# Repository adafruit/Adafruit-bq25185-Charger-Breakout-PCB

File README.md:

## Adafruit bq25185 USB / DC / Solar Lithium Ion/Polymer Charger PCB

<a href="http://www.adafruit.com/products/6091"><br/>
Click here to purchase one from the Adafruit shop</a>

PCB files for the Adafruit bq25185 USB / DC / Solar Lithium Ion/Polymer Charger. 

Format is EagleCAD schematic and board layout
* https://www.adafruit.com/product/6091

### Description

We're always on the look out for better ways to make projects portable: being able to charge your battery in the most convenient manner will let projects run no matter what power is available. The Adafruit bq25185 USB / DC / Solar Charger Board uses the new bq25185 is a nifty charger chip which has a lot of flexibility for different kinds of batteries (LiPoly, LiIon or LiFePO4), charging rates (250mA, 500mA, or 1A) and power sources (USB, DC or solar). It's also a great value, so it's a good upgrade from MCP73833 or MCP73831-based charger boards.

To let folks really explore what this chip can do, we made a basic breakout board with all the things we find most useful: two ways to power/charge including a solar-friendly DC input, adjustable current and voltage, power path management, and status and control I/O.

* USB Type C connector with 5.1k CC resistors so it will work with any computer or power supply to get 5V and up to 1A
* Separate DC or Solar Input - Two pads on the side can be used to connect a 5 ~ 18V power supply, which can be used instead of USB. If the input is a solar panel, the charging chip will adjust the current draw so that the voltage does not dip below the battery, thus optimizing the solar power input. No large capacitor needed to stabilize it, and you get near-MPPT capability without the cost and complexity of MPPT.
* Default charge rate of 1A, but you can cut the IS jumper on the front and solder either jumper on the back to set the rate to 500mA or 250mA
* Default 3.7V nominal / 4.2V max battery chemistry/voltage for all modern 1-cell LiPoly or LiIon batteries. You can set this to 3.2V / 3.65V for LiFePO4 batteries by cutting the VS jumper on the front and soldering a jumper on the back
* Power Path to Load - If the load connector is drawing current while the USB / DC/Solar power is attached, it will default to drawing current from the charger and any left over current will go to the battery. That keeps your battery from constantly charging/discharging which will reduce the battery life. The max draw from USB / DC / Solar is still 1A, if you need more current it will come from the battery and the chip can provide up to 3A current spikes from the battery to the load output!
* Regulated 4.5V-max Load Output - no matter what voltage you have on the USB or DC / solar inputs, the Load output port will never go above 4.5V due to an internal voltage regulator. Keep this in mind, though, when dealing with high currents and high DC voltages as the LDO will make the board start to overheat and throttle the current.
* Three Status LEDs - Orange Charging LED, red Fault LED, and Green Power Good LED. The charge/fault pins are also available on the left side breakout pads.
* Thermistor - cut the TH trace and you can connect a 10K thermistor to the TH pad which will adjust the charge rate to keep the battery from overheating.
* Chip Enable to disable the charger.
* Mounting holes!

This board is pretty much plug-and-play. Change any jumpers you like and then connect your battery to the BATT port, and the LOAD goes to your circuit. Don't forget the LOAD will never go above 4.5V, but it can go as low as 3.0V if the battery is nearly empty. You can monitor the voltage on the battery and load via the secondary pads on the right side, if necessary.

To use with solar, pick up a 5~7V solar panel, and either cut the connector off to wire it directly, or use a 2.1mm adapter cable plus a 2.1mm terminal block to get two wires for the DC Input port.

If you need a board with higher charge current or a DC plug already on-board, check out the bq24074 which has up to 1.5A charge rate and a on-board 2.1mm DC jack.

### License

Adafruit invests time and resources providing this open source design, please support Adafruit and open-source hardware by purchasing products from [Adafruit](https://www.adafruit.com)!

Designed by Limor Fried/Ladyada for Adafruit Industries.

Creative Commons Attribution/Share-Alike, all text above must be included in any redistribution. 
See license.txt for additional details.

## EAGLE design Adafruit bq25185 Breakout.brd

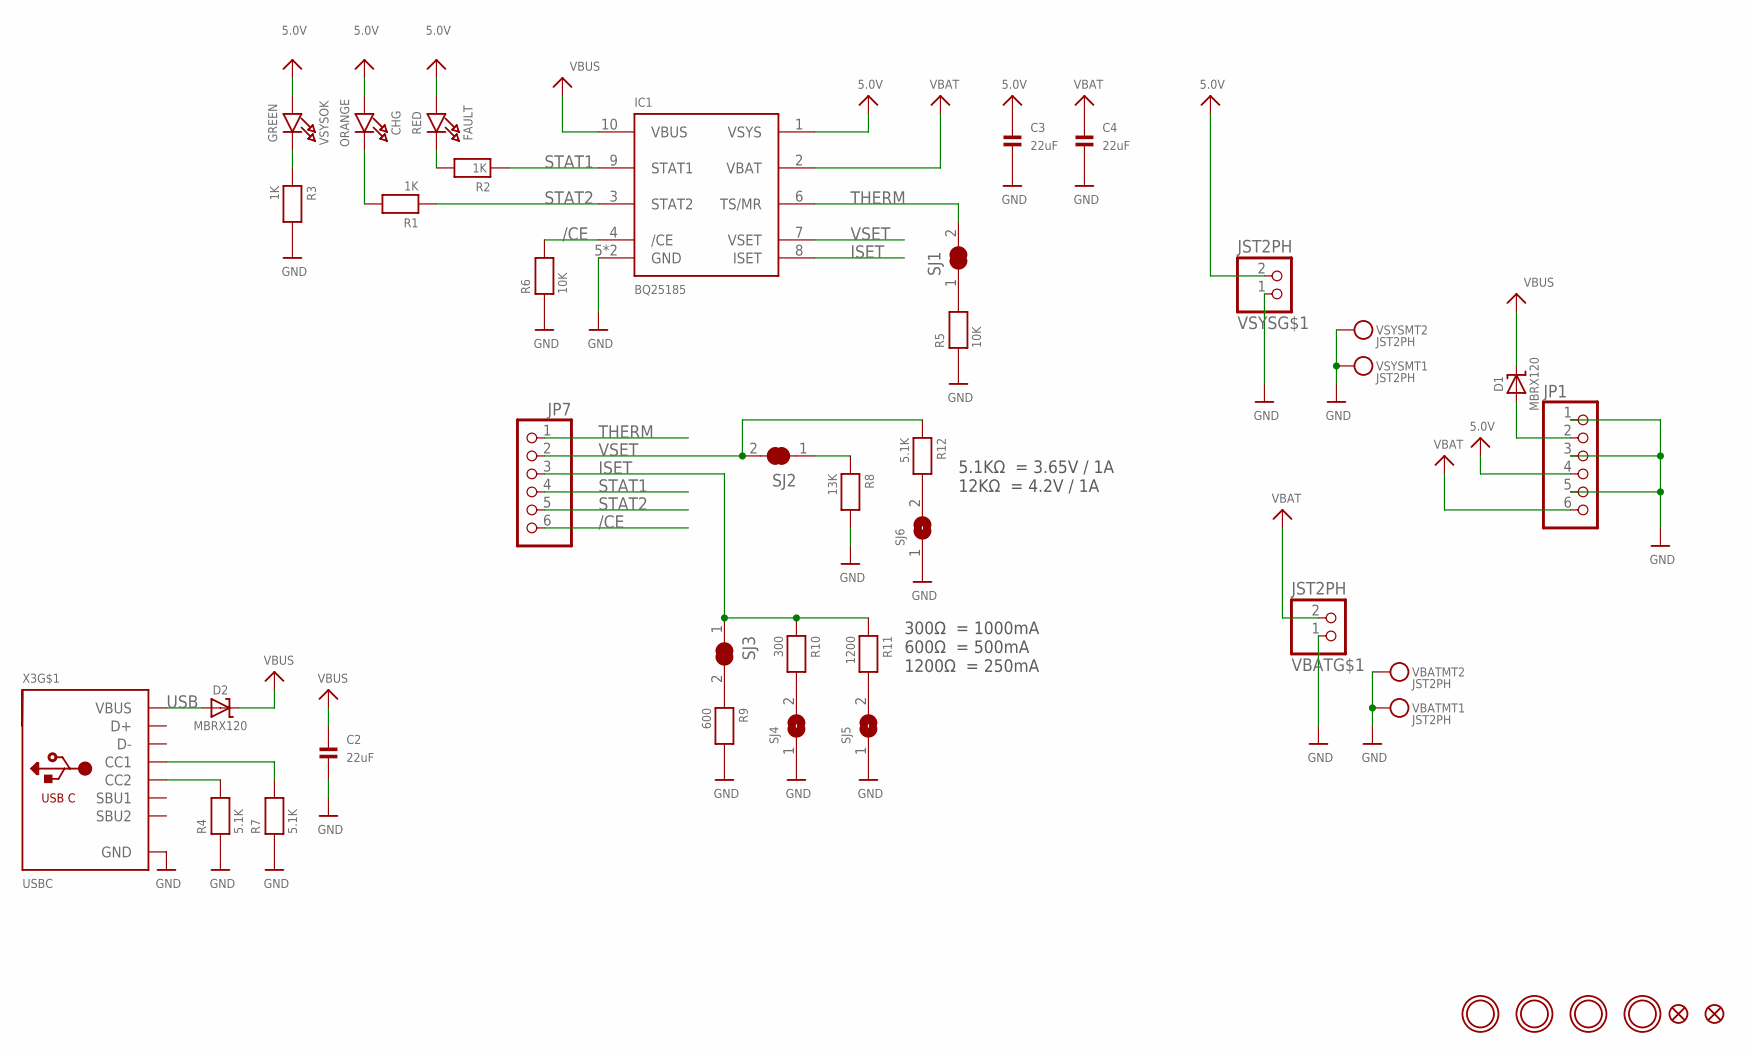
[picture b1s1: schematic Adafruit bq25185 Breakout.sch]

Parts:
C2, C3, C4: 22uF; 0805-NO
CHG: ORANGE; CHIPLED_0805_NOOUTLINE
D1, D2: MBRX120; SOD-123FL
FAULT: RED; CHIPLED_0805_NOOUTLINE
IC1: BQ25185; WSON10
JP1: HEADER-1X6OVALWAVE; 1X06_OVALWAVE
JP2, JP4: FIDUCIAL1.5X3; FIDUCIAL_0.5MM
JP7: HEADER-1X676MIL; 1X06_ROUND_76
R1, R2, R3: 1K; 0603-NO
R4, R7, R12: 5.1K; 0603-NO
R5, R6: 10K; 0603-NO
R8: 13K; 0603-NO
R9: 600; 0603-NO
R10: 300; 0603-NO
R11: 1200; 0603-NO
SJ1, SJ2, SJ3: SOLDERJUMPER_CLOSED; SOLDERJUMPER_CLOSEDWIRE
SJ4, SJ5, SJ6: SOLDERJUMPER; SOLDERJUMPER_ARROW_NOPASTE
U$11, U$16, U$18, U$19: MOUNTINGHOLE2.5; MOUNTINGHOLE_2.5_PLATED
VBAT: JST2PH; JSTPH2_BATT
VSYS: JST2PH; JSTPH2_BATT
VSYSOK: GREEN; CHIPLED_0805_NOOUTLINE
X3: USBC; USB_C_CUSB31-CFM2AX-01-X

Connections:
5.0V: C3.1, CHG.A, FAULT.A, IC1.1 (VSYS), JP1.4, VSYS.2, VSYSOK.A
/CE: IC1.4 (/CE), JP7.6, R6.2
GND: C2.2, C3.2, C4.2, IC1.5 (GND), IC1.PAD (GND), JP1.1, JP1.3, JP1.5, R3.2, R4.1, R5.1, R6.1, R7.1, R8.2, R9.2, SJ4.1, SJ5.1, SJ6.1, VBAT.1, VBAT.NC1, VBAT.NC2, VSYS.1, VSYS.NC1, VSYS.NC2, X3.A1B12 (GND), X3.B1A12 (GND)
ISET: IC1.8 (ISET), JP7.3, R10.1, R11.1, SJ3.1
unnamed: CHG.C, R1.2
unnamed: FAULT.C, R2.2
unnamed: R8.1, SJ2.1
unnamed: R4.2, X3.B5 (CC2)
unnamed: R5.2, SJ1.1
unnamed: R7.2, X3.A5 (CC1)
unnamed: R9.1, SJ3.2
unnamed: R10.2, SJ4.2
unnamed: R11.2, SJ5.2
unnamed: R12.2, SJ6.2
unnamed: D1.A, JP1.2
unnamed: R3.1, VSYSOK.C
STAT1: IC1.9 (STAT1), JP7.4, R2.1
STAT2: IC1.3 (STAT2), JP7.5, R1.1
THERM: IC1.6 (TS/MR), JP7.1, SJ1.2
USB: D2.A, X3.A4B9 (VBUS), X3.B4A9 (VBUS)
VBAT: C4.1, IC1.2 (VBAT), JP1.6, VBAT.2
VBUS: C2.1, D1.C, D2.C, IC1.10 (VBUS)
VSET: IC1.7 (VSET), JP7.2, R12.1, SJ2.2

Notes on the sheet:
300Ω = 1000mA 600Ω = 500mA 1200Ω = 250mA
5.1KΩ = 3.65V / 1A 12KΩ = 4.2V / 1A

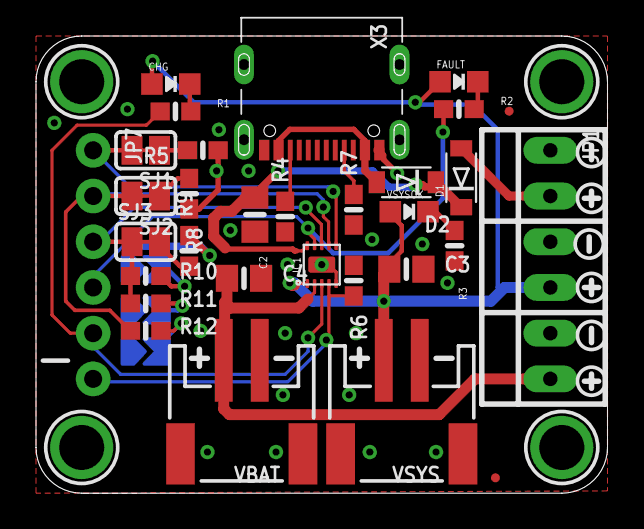
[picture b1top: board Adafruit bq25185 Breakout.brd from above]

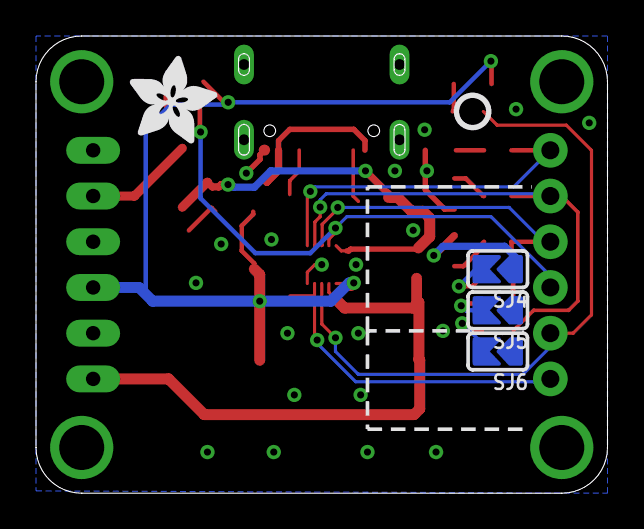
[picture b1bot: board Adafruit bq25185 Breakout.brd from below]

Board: 2 copper layers, 31.8 x 25.4 mm, 69 parts (13 on the bottom side), 23 nets.

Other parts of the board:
PLABEL0: PLABEL0
PLABEL1: PLABEL1
PLABEL2: PLABEL2
PLABEL3: PLABEL3
PLABEL4: PLABEL4
PLABEL5: PLABEL5
PLABEL6: PLABEL6
PLABEL7: PLABEL7
PLABEL8: PLABEL8
PLABEL9: PLABEL9
PLABEL10: PLABEL10
PLABEL11: PLABEL11
PLABEL12: PLABEL12
PLABEL13: PLABEL13
PLABEL14: PLABEL14
PLABEL15: PLABEL15
PLABEL16: PLABEL16
PLABEL17: PLABEL17
PLABEL18: PLABEL18
PLABEL19: PLABEL19
PLABEL20: PLABEL20
PLABEL21: PLABEL21
PLABEL22: PLABEL22
U$23, U$27, U$28: SYMBOL_PLUS
U$24, U$25, U$26: SYMBOL_MINUS
U$46: ADAFRUIT_5MM
U$47: PCBFEAT-REV-040

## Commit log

2024-11-21 cookiecutter
2026-03-02 add b1, updated back silk
    https://github.com/adafruit/Adafruit-bq25185-Charger-Breakout-PCB/issues/2
